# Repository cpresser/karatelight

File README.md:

# Karatelight
This repository contains firmware and Hardware design files for the Karatelight 8/16 channel RGB LED Dimmer.

# Firmware
`karate_xc8.X` and `karate_v2.X` contain the firmware for the device
* both are *MPLAB X* projects. I used version 1.41 to work with them, but any newer version should work as well.
* `karate_xc8.X` can be build with microchips XC8 compiler
* `karate_v2.X` requires the MCC18 compiler
* You might want to adjust the USB VID/PID when building this
* The code is based on microchip examples, so for most part of it the microchip licence applies. Those files have a intact microchip header-
* All other files are GPL v2. see gpl-2.0.txt
* Most files are encoded iso8859-1, some might be utf-8

`fsUSB_Bootloader` contains a bootloader for the device. Its software from microchip, just slightly adjusted to the hardware (Fuses, Switch).

# Hardware
* The Hardware is licensed CERN OHL version 1.2
* Both the base-board and the extension-board are included
* The files were created using Cadsoft Eagle 6.3.
* Only the latest revision (v06b) of the board is in this repository. If you need the files for a previous version, please contact me.
* The files `20150310_KarateLight_Haka.zip` and `20150310_KarateLight-Exp_Haka.zip` were used for board production
* The folder `stencil` contains files used to create a stencil and stencil holder with a laser-cutter.
* There is a BOM with links to reichelt, digikey and mouser article numbers. Prices are most likely outdated.

# Software
The device can be used with various software packages. Some of them are
* https://github.com/durchflieger/DFAtmo
* https://github.com/OpenLightingProject/ola/
* https://github.com/einmalacht/enigmalight/
* atmolightd-plugin for Engima2 based set-top boxes
* AtmoWin

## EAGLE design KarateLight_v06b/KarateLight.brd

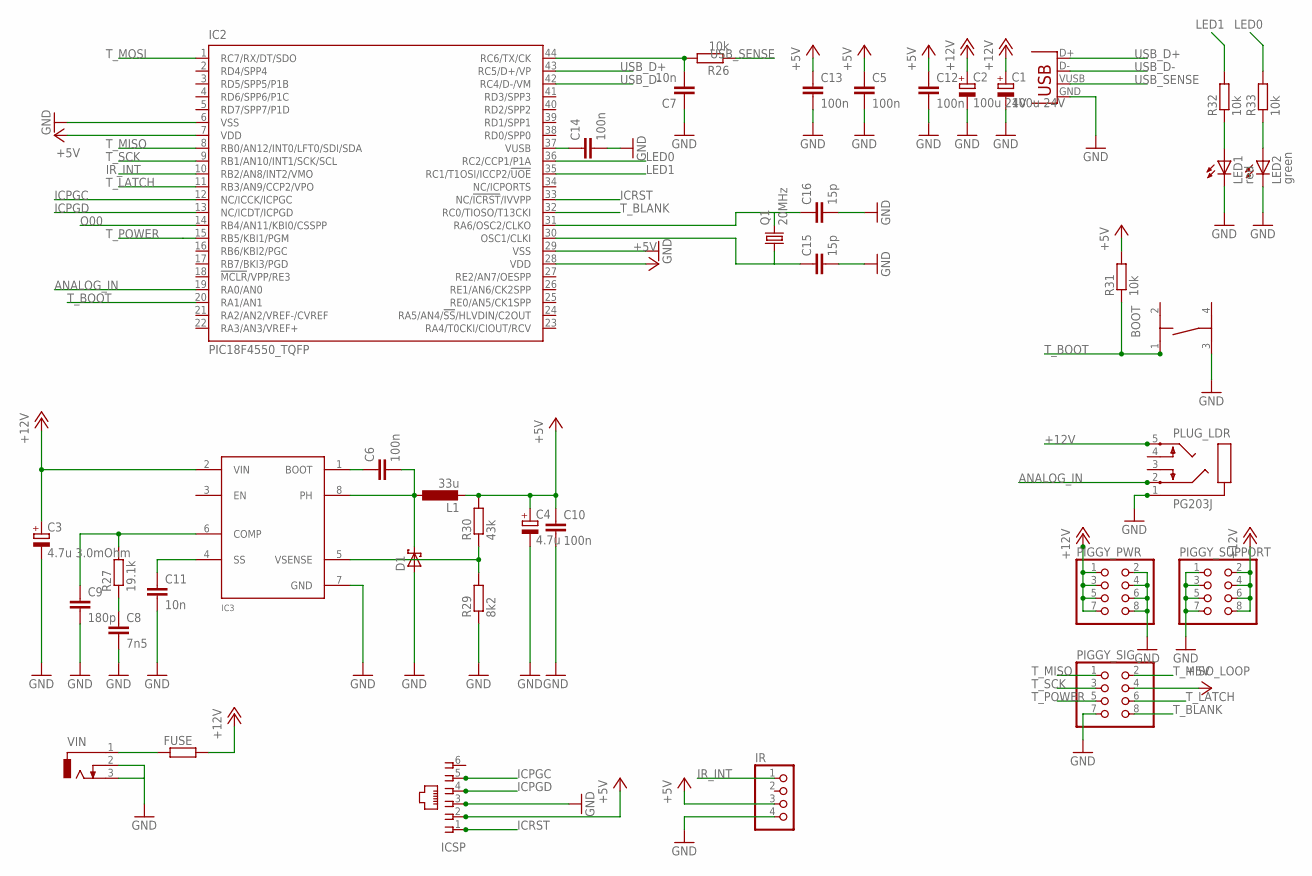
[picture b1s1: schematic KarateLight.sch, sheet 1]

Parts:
BOOT: TASTER-9314_SMD
C1, C2: 100u 24V; 153CLV-0605
C3: 4.7u 3.0mOhm; 153CLV-0405
C4: 4.7u; 153CLV-0405
C5, C13, C14: 100n; C0805K
C6, C10, C12: 100n; C0603
C7, C11: 10n; C0603
C8: 7n5; C0603
C9: 180p; C0603
C15, C16: 15p; C0603
D1: SCHOTTKY-DIODESMD; SMB
FUSE: R-EU_R4527; R4527
IC2: PIC18F4550_TQFP; TQFP44
IC3: TPS54232; SO-08
ICSP: 520250-3
IR: PINHD-1X4; 1X04
L1: 33u; PIS2816
LED1: red; CHIP-LED0805
LED2: green; CHIP-LED0805
PIGGY_PWR: PINHD-2X4; 2X04
PIGGY_SIG: PINHD-2X4; 2X04
PIGGY_SUPPORT: PINHD-2X4; 2X04
PLUG_LDR: PG203J
PLUG_USB: USB-B-S; USB-B-SMT
Q1: 20MHz; HC49UP
R26, R31, R32, R33: 10k; R0603
R27: 19.1k; R0603
R29: 8k2; R0603
R30: 43k; R0603
VIN: DCJ0303

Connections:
+5V: C4.+, C5.1, C10.1, C12.1, C13.1, IC2.7 (VDD), IC2.28 (VDD), ICSP.2, IR.3, L1.2, PIGGY_SIG.4, R30.2, R31.2; also elsewhere on the board
+12V: C1.+, C2.+, C3.+, FUSE.2, IC3.2 (VIN), PIGGY_PWR.1, PIGGY_PWR.3, PIGGY_PWR.5, PIGGY_PWR.7, PIGGY_SUPPORT.2, PIGGY_SUPPORT.4, PIGGY_SUPPORT.6, PIGGY_SUPPORT.8, PLUG_LDR.5; also elsewhere on the board
ANALOG_IN: IC2.19 (RA0/AN0), PLUG_LDR.2
BOOST: C6.2, D1.C, IC3.8 (PH), L1.1
GND: BOOT.3, C1.-, C2.-, C3.-, C4.-, C5.2, C7.1, C8.2, C9.2, C10.2, C11.2, C12.2, C13.2, C14.2, C15.2, C16.2, D1.A, IC2.6 (VSS), IC2.29 (VSS), IC3.7 (GND), ICSP.3, IR.4, LED1.C, LED2.C, PIGGY_PWR.2, PIGGY_PWR.4, PIGGY_PWR.6, PIGGY_PWR.8, PIGGY_SIG.7, PIGGY_SUPPORT.1, PIGGY_SUPPORT.3, PIGGY_SUPPORT.5, PIGGY_SUPPORT.7, PLUG_LDR.1, PLUG_USB.GND, R29.1, VIN.2, VIN.3; also elsewhere on the board
ICPGC: IC2.12 (NC/ICCK/ICPGC), ICSP.5
ICPGD: IC2.13 (NC/ICDT/ICPGD), ICSP.4
ICRST: IC2.33 (NC/!ICRST!/IVVPP), ICSP.1
IR_INT: IC2.10 (RB2/AN8/INT2/VMO), IR.1
LED0: IC2.36 (RC2/CCP1/P1A), R33.2
LED1: IC2.35 (RC1/T1OSI/ICCP2/!UOE), R32.2
unnamed: C14.1, IC2.37 (VUSB)
unnamed: C15.1, IC2.30 (OSC1/CLKI), Q1.1
unnamed: C16.1, IC2.31 (RA6/OSC2/CLKO), Q1.2
unnamed: C8.1, R27.1
unnamed: C7.2, IC2.44 (RC6/TX/CK), R26.2
unnamed: LED1.A, R32.1
unnamed: C9.1, IC3.6 (COMP), R27.2
unnamed: LED2.A, R33.1
unnamed: C11.1, IC3.4 (SS)
unnamed: IC3.5 (VSENSE), R29.2, R30.1
unnamed: C6.1, IC3.1 (BOOT)
O00: IC2.14 (RB4/AN11/KBI0/CSSPP); also elsewhere on the board
T_BLANK: IC2.32 (RC0/TIOSO/T13CKI), PIGGY_SIG.8; also elsewhere on the board
T_BOOT: BOOT.1, IC2.20 (RA1/AN1), R31.1
T_LATCH: IC2.11 (RB3/AN9/CCP2/VPO), PIGGY_SIG.6; also elsewhere on the board
T_MISO: IC2.8 (RB0/AN12/INT0/LFT0/SDI/SDA), PIGGY_SIG.1
T_MISO_LOOP: PIGGY_SIG.2; also elsewhere on the board
T_MOSI: IC2.1 (RC7/RX/DT/SDO); also elsewhere on the board
T_POWER: IC2.15 (RB5/KBI1/PGM), PIGGY_SIG.5; also elsewhere on the board
T_SCK: IC2.9 (RB1/AN10/INT1/SCK/SCL), PIGGY_SIG.3; also elsewhere on the board
USB_D+: IC2.43 (RC5/D+/VP), PLUG_USB.D+
USB_D-: IC2.42 (RC4/D-/VM), PLUG_USB.D-
USB_SENSE: PLUG_USB.VUSB (VBUS), R26.1
VIN: FUSE.1, VIN.1

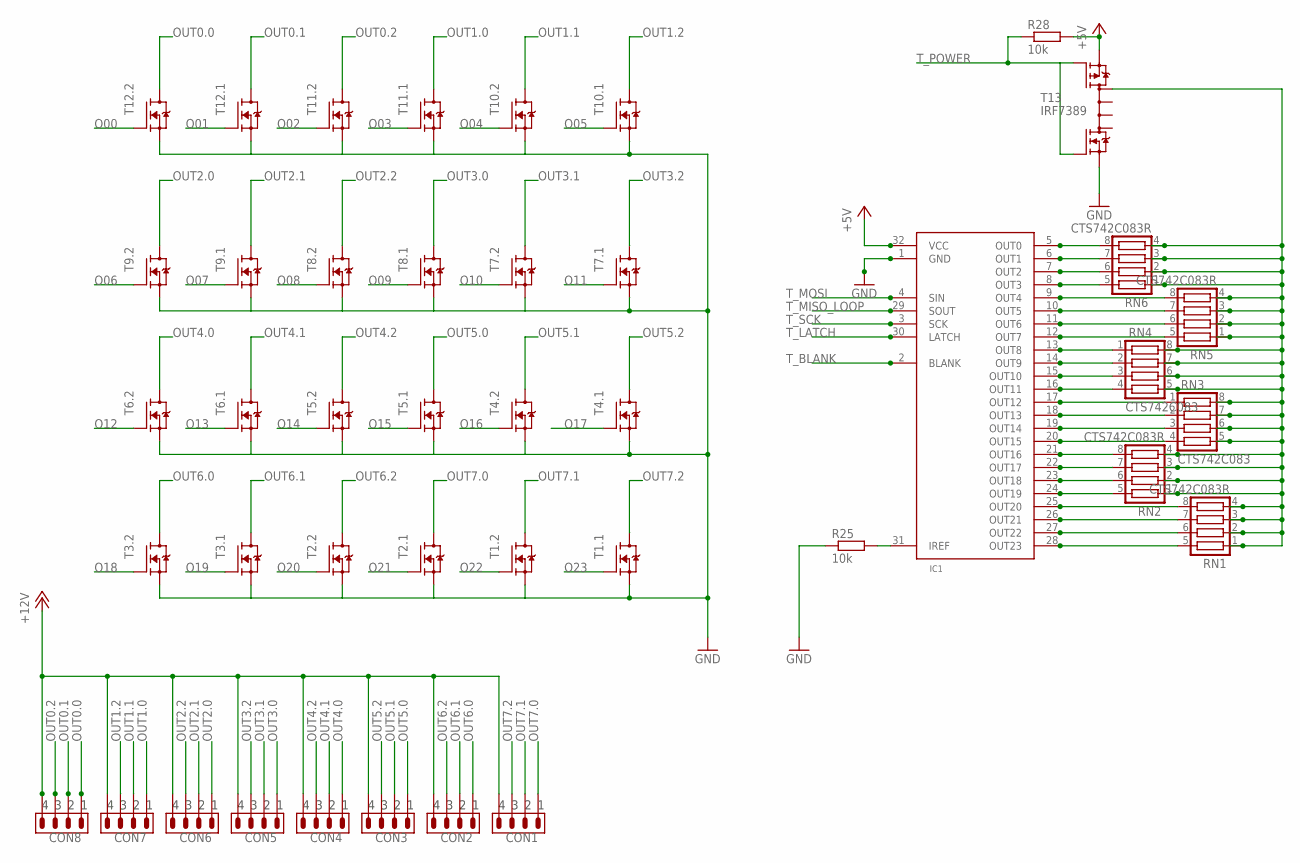
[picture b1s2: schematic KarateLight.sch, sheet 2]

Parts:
CON1, CON2, CON3, CON4, CON5, CON6, CON7, CON8: PINHEAD_4W; MA04-1
IC1: TLC5947; TSSOP32
R25, R28: 10k; R0603
RN1, RN2, RN5, RN6: CTS742C083R; CTS742C083
RN3, RN4: CTS742C083
T1, T2, T3, T4, T5, T6, T7, T8, T9, T10, T11, T12: IRF7103; SO08-IRF
T13: IRF7389; SO08-IRF

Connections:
+5V: IC1.32 (VCC), R28.2, T13.3 (P-S); also elsewhere on the board
+12V: CON1.4, CON2.4, CON3.4, CON4.4, CON5.4, CON6.4, CON7.4, CON8.4; also elsewhere on the board
FET-ONOFF: RN1.1, RN1.2, RN1.3, RN1.4, RN2.1, RN2.2, RN2.3, RN2.4, RN3.5, RN3.6, RN3.7, RN3.8, RN4.5, RN4.6, RN4.7, RN4.8, RN5.1, RN5.2, RN5.3, RN5.4, RN6.1, RN6.2, RN6.3, RN6.4, T13.5 (D)
GND: IC1.1 (GND), R25.1, T1.1 (S), T1.3 (S), T2.1 (S), T2.3 (S), T3.1 (S), T3.3 (S), T4.1 (S), T4.3 (S), T5.1 (S), T5.3 (S), T6.1 (S), T6.3 (S), T7.1 (S), T7.3 (S), T8.1 (S), T8.3 (S), T9.1 (S), T9.3 (S), T10.1 (S), T10.3 (S), T11.1 (S), T11.3 (S), T12.1 (S), T12.3 (S), T13.1 (N-S); also elsewhere on the board
unnamed: IC1.31 (IREF), R25.2
O00: IC1.5 (OUT0), RN6.8 (5), T12.4 (G); also elsewhere on the board
O01: IC1.6 (OUT1), RN6.7 (6), T12.2 (G)
O02: IC1.7 (OUT2), RN6.6 (7), T11.4 (G)
O03: IC1.8 (OUT3), RN6.5 (8), T11.2 (G)
O04: IC1.9 (OUT4), RN5.8 (5), T10.4 (G)
O05: IC1.10 (OUT5), RN5.7 (6), T10.2 (G)
O06: IC1.11 (OUT6), RN5.6 (7), T9.4 (G)
O07: IC1.12 (OUT7), RN5.5 (8), T9.2 (G)
O08: IC1.13 (OUT8), RN4.1, T8.4 (G)
O09: IC1.14 (OUT9), RN4.2, T8.2 (G)
O10: IC1.15 (OUT10), RN4.3, T7.4 (G)
O11: IC1.16 (OUT11), RN4.4, T7.2 (G)
O12: IC1.17 (OUT12), RN3.1, T6.4 (G)
O13: IC1.18 (OUT13), RN3.2, T6.2 (G)
O14: IC1.19 (OUT14), RN3.3, T5.4 (G)
O15: IC1.20 (OUT15), RN3.4, T5.2 (G)
O16: IC1.21 (OUT16), RN2.8 (5), T4.4 (G)
O17: IC1.22 (OUT17), RN2.7 (6), T4.2 (G)
O18: IC1.23 (OUT18), RN2.6 (7), T3.4 (G)
O19: IC1.24 (OUT19), RN2.5 (8), T3.2 (G)
O20: IC1.25 (OUT20), RN1.8 (5), T2.4 (G)
O21: IC1.26 (OUT21), RN1.7 (6), T2.2 (G)
O22: IC1.27 (OUT22), RN1.6 (7), T1.4 (G)
O23: IC1.28 (OUT23), RN1.5 (8), T1.2 (G)
OUT0.0: CON8.1, T12.6 (D)
OUT0.1: CON8.2, T12.8 (D)
OUT0.2: CON8.3, T11.6 (D)
OUT1.0: CON7.1, T11.8 (D)
OUT1.1: CON7.2, T10.6 (D)
OUT1.2: CON7.3, T10.8 (D)
OUT2.0: CON6.1, T9.6 (D)
OUT2.1: CON6.2, T9.8 (D)
OUT2.2: CON6.3, T8.6 (D)
OUT3.0: CON5.1, T8.8 (D)
OUT3.1: CON5.2, T7.6 (D)
OUT3.2: CON5.3, T7.8 (D)
OUT4.0: CON4.1, T6.6 (D)
OUT4.1: CON4.2, T6.8 (D)
OUT4.2: CON4.3, T5.6 (D)
OUT5.0: CON3.1, T5.8 (D)
OUT5.1: CON3.2, T4.6 (D)
OUT5.2: CON3.3, T4.8 (D)
OUT6.0: CON2.1, T3.6 (D)
OUT6.1: CON2.2, T3.8 (D)
OUT6.2: CON2.3, T2.6 (D)
OUT7.0: CON1.1, T2.8 (D)
OUT7.1: CON1.2, T1.6 (D)
OUT7.2: CON1.3, T1.8 (D)
T_BLANK: IC1.2 (BLANK); also elsewhere on the board
T_LATCH: IC1.30 (LATCH); also elsewhere on the board
T_MISO_LOOP: IC1.29 (SOUT); also elsewhere on the board
T_MOSI: IC1.4 (SIN); also elsewhere on the board
T_POWER: R28.1, T13.2 (N-G), T13.4 (P-G); also elsewhere on the board
T_SCK: IC1.3 (SCK); also elsewhere on the board

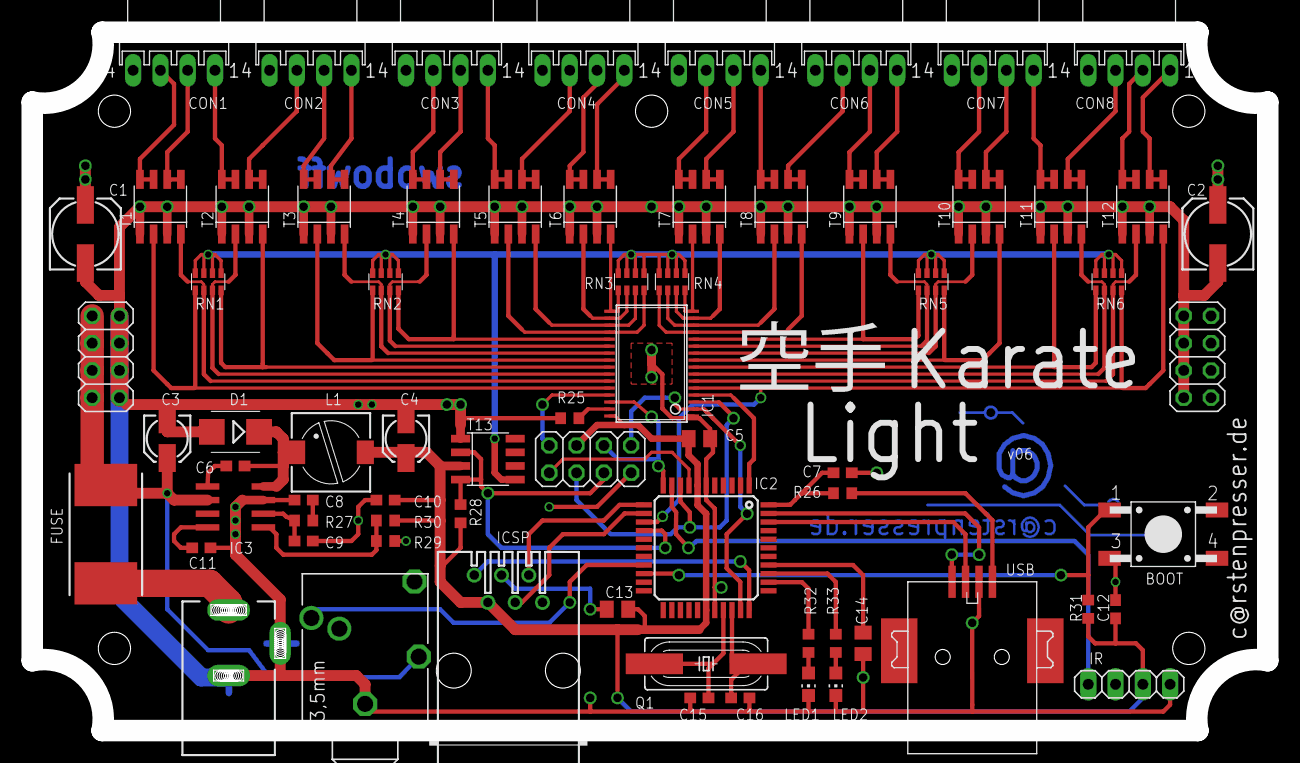
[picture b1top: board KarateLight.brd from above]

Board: 2 copper layers, 115.0 x 65.0 mm, 70 parts (0 on the bottom side), 84 nets.

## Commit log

2017-12-09 Add firmware and hardware files
